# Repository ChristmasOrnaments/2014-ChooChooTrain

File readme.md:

This is the second ornament in my DIY ornament series, the **Choo Choo Train**

***

This ornament is very similar to the [original 2013 ornament](https://github.com/ChristmasOrnaments/2013-Snowman), with only a few minor changes. The image in the silkscreen has changed (it's a train). The locations of the LEDs have change, and so the patterns that it produces were also changed to represent the wheels of the train in motion. Another change was to the ICSP header on the board. I made a small [pogo-pin adapter](https://github.com/timtilities/Pogo-Pin-ICSP-Adapter) so the header wouldn't take up as much room. It's much easier to use (and also easier to design board traces around). I also removed the extra LED from the back of the board, since I never used it. I had intended to use it as a "low battery" indicator, but the brightness of the LEDs does a fine job of that anyway.

The new pogo adapter:

Here's the ornament in action:
<!-- https://github.com/user-attachments/assets/bbaf6b06-1da1-494d-bd4b-d39d66976917 -->

### Compiling

* Install [ATTinyCore](https://github.com/spencekonde/attinycore) using the boards manager
* Select **Attiny25/45/85 (No bootloader)** from the boards list
* Set the *Clock source* to **4MHz (internal)** (With newer versions, you may need to use 8MHz with a scalar variable to lower it to 4MHz)
* Set *B.O.D* to **Disabled**
* Select **Burn Bootloader** to write the changes
* Compile and write the program to the MCU

If using another method to program the MCU, just remember you need to set the fuses properly both for correct speed and for the power saving features. The fuses (for an ATTINY45) should be:

Low: C3  
High: DF  
Extended: FF

You can see the effect of different fuse settings (and their values) [here](http://www.engbedded.com/fusecalc/).

### Resources

**Charlieplexing Code using a byte array:**  
[https://www.instructables.com/CharliePlexed-LED-string-for-the-Arduino/](https://www.instructables.com/CharliePlexed-LED-string-for-the-Arduino/)

**Battery calculator:**  
[http://oregonembedded.com/batterycalc.htm](http://oregonembedded.com/batterycalc.htm)

**Power saving information:**  
[http://www.gammon.com.au/forum/?id=11497](http://www.gammon.com.au/forum/?id=11497)  
[http://www.insidegadgets.com/2011/02/05/reduce-attiny-power-consumption-by-sleeping-with-the-watchdog-timer](http://www.insidegadgets.com/2011/02/05/reduce-attiny-power-consumption-by-sleeping-with-the-watchdog-timer/)  
[http://www.nongnu.org/avr-libc/user-manual/group\_\_avr\_\_power.html](http://www.nongnu.org/avr-libc/user-manual/group__avr__power.html)

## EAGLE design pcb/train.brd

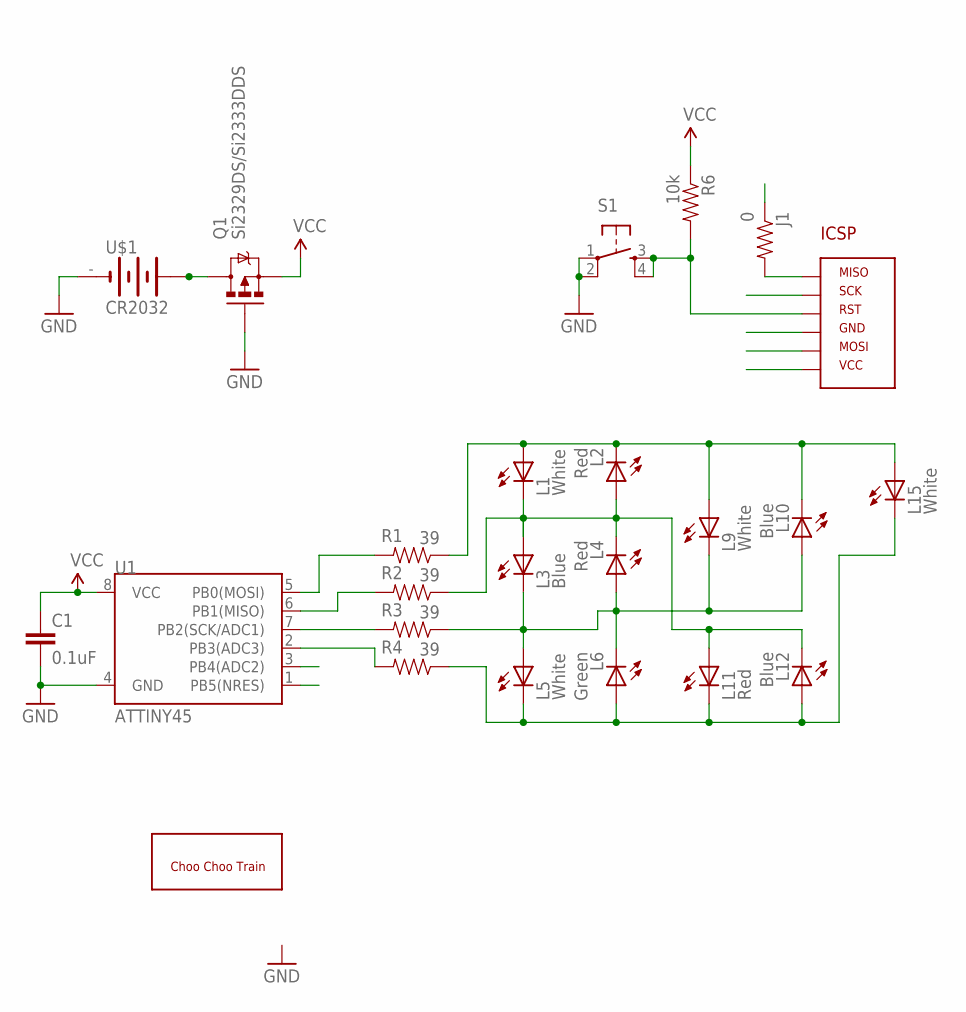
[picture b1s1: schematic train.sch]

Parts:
C1: 0.1uF; 0805
J1: 0; 0805
L1, L5: White; LED-0805-RED
L2, L4: Red; LED-0805-RED
L3, L12: Blue; LED-0805-RED
L6: Green; LED-0805-BLUE
L9: White; LED-0805-YELLOW
L10: Blue; LED-0805-BLUE
L11: Red; LED-0805-BLUE
L15: White; LED-0805-BLUE
Q1: Si2329DS/Si2333DDS; SOT23-3
R1, R2, R3, R4: 39; 0805
R6: 10k; 0805
S1: TAC_SWITCHSMD; TACTILE_SWITCH_SMD
U1: ATTINY45; SO08-EIAJ
U$1: CR2032; BAT-HLD-001
U$2: AVR_ICSP_6P1X6; AVR_ICSP_1X6_SMD
U$3: 5X6_CHOOCHOOTRAIN; CHOOCHOO

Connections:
GND: C1.2, Q1.1 (G), S1.1, S1.2, U1.4 (GND), U$1.-, U$2.P6 (GND)
L12: L1.C, L2.A, L3.A, L4.C, L11.A, L12.C, R2.1
MISO: J1.1, R2.2, U1.6 (PB1(MISO))
MOSI: R1.2, U1.5 (PB0(MOSI)), U$2.P4 (MOSI)
unnamed: Q1.3 (D), U$1.+@1 (+), U$1.+@2 (+)
unnamed: L3.C, L4.A, L5.A, L6.C, L9.C, L10.A, R3.1
unnamed: R4.2, U1.2 (PB3(ADC3))
unnamed: L1.A, L2.C, L9.A, L10.C, L15.A, R1.1
unnamed: J1.2, U$2.P5 (MISO)
unnamed: L5.C, L6.A, L11.C, L12.A, L15.C, R4.1
RST: R6.2, S1.3, S1.4, U1.1 (PB5(NRES)), U$2.P3 (RST)
SCK: R3.2, U1.7 (PB2(SCK/ADC1)), U$2.P2 (SCK)
VCC: C1.1, Q1.2 (S), R6.1, U1.8 (VCC), U$2.P1 (VCC)

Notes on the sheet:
ICSP

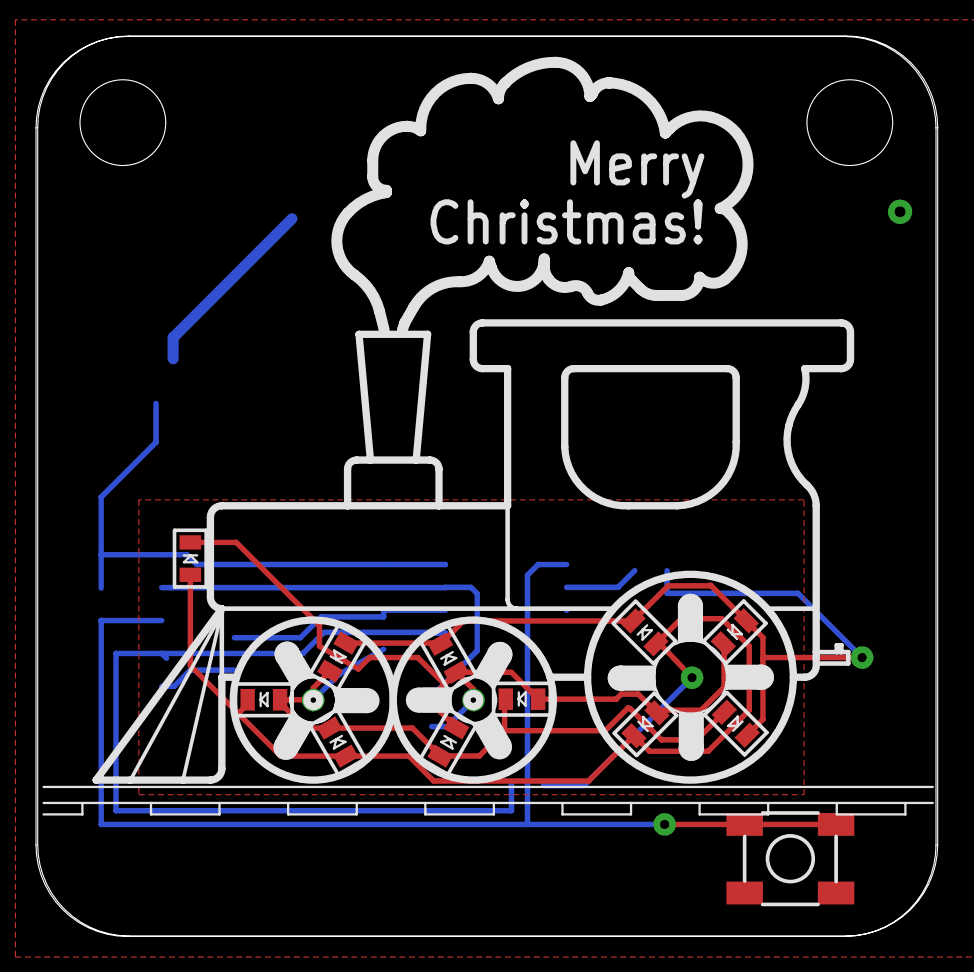
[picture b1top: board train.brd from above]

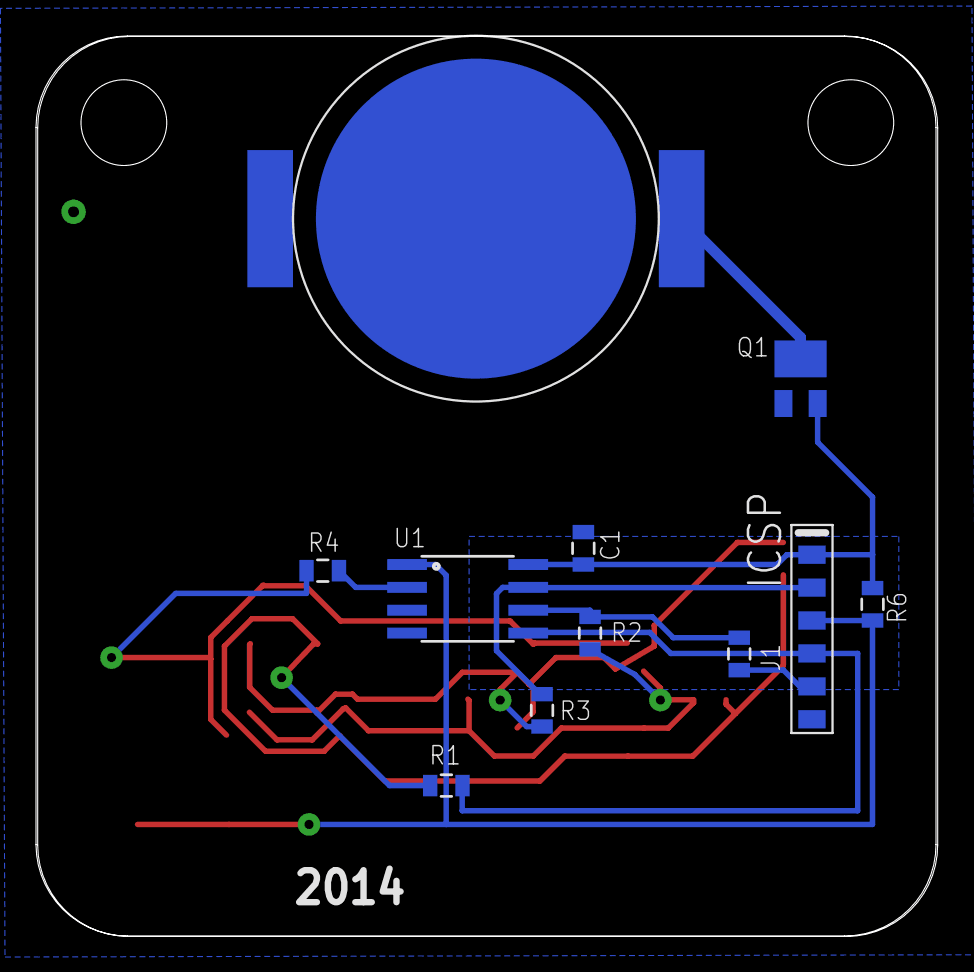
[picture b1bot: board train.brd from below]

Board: 2 copper layers, 50.1 x 50.0 mm, 24 parts (11 on the bottom side), 13 nets.

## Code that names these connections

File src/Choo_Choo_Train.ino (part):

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// ATMEL ATTINY85 / ARDUINO
//
//                            ____
//         (D5/A0) RST/PB5  1|*   |8  VCC
//   PWM   (D3/A3)     PB3  2|    |7  PB2  (D2/A1)
//   PWM   (D4/A2)     PB4  3|    |6  PB1  (D1)     PWM
//                     GND  4|____|5  PB0  (D0)     PWM


#include <avr/pgmspace.h>
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
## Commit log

2026-03-22 initial
2026-03-22 replaced mp4 video with a gif

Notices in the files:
parts and their libraries:
SparkFun: Licensing: CC v3.0 Share-Alike You are welcome to use this library for commercial purposes.
